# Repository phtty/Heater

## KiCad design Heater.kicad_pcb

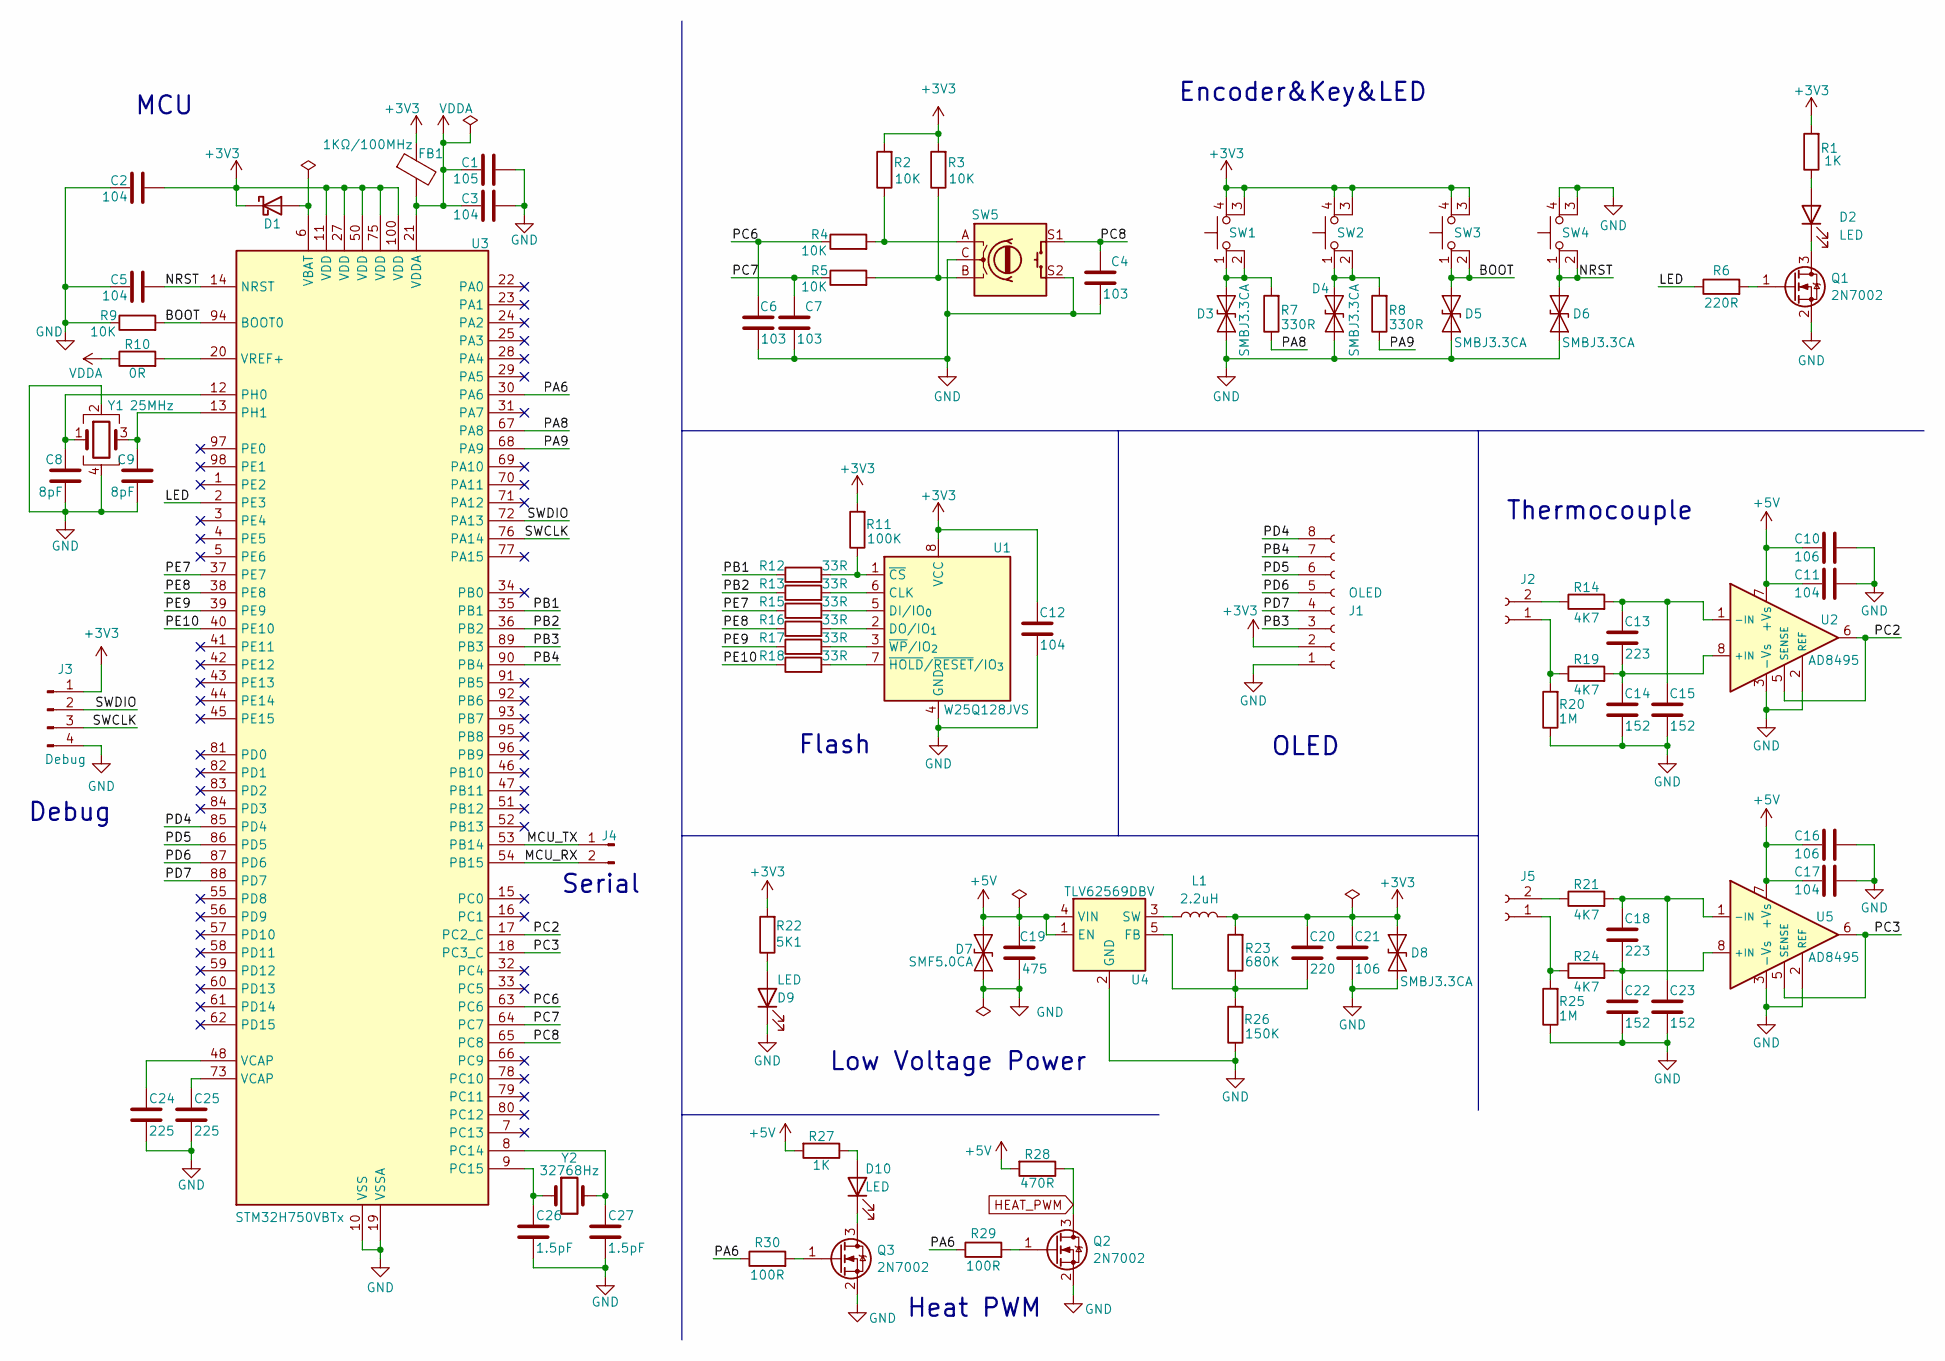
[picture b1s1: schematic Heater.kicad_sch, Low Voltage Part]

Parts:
C1: 105; C_0603_1608Metric_Pad1.08x0.95mm_HandSolder
C2, C3, C5, C11, C12, C17: 104; C_0603_1608Metric_Pad1.08x0.95mm_HandSolder
C4, C6, C7: 103; C_0603_1608Metric_Pad1.08x0.95mm_HandSolder
C8, C9: 8pF; C_0603_1608Metric_Pad1.08x0.95mm_HandSolder
C10, C16, C21: 106; C_0603_1608Metric_Pad1.08x0.95mm_HandSolder
C13, C18: 223; C_0603_1608Metric_Pad1.08x0.95mm_HandSolder
C14, C15, C22, C23: 152; C_0603_1608Metric_Pad1.08x0.95mm_HandSolder
C19: 475; C_0603_1608Metric_Pad1.08x0.95mm_HandSolder
C20: 220; C_0603_1608Metric_Pad1.08x0.95mm_HandSolder
C24, C25: 225; C_0603_1608Metric_Pad1.08x0.95mm_HandSolder
C26, C27: 1.5pF; C_0603_1608Metric_Pad1.08x0.95mm_HandSolder
D1: D_Schottky; D_SOD-123
D2, D9, D10: LED; D_0603_1608Metric_Pad1.05x0.95mm_HandSolder
D3, D4, D5, D6, D8: SMBJ3.3CA; D_SMB_Handsoldering
D7: SMF5.0CA; D_SOD-123F
FB1: 1KΩ/100MHz; C_0603_1608Metric_Pad1.08x0.95mm_HandSolder
J1: OLED; PinHeader_1x08_P2.54mm_Vertical
J2, J5: Conn_01x02_Socket; PinHeader_1x02_P2.54mm_Vertical
J3: Debug; PinHeader_1x04_P2.54mm_Vertical
J4: Conn_01x02_Pin; PinHeader_1x02_P2.54mm_Vertical
L1: 2.2uH; L_0603_1608Metric_Pad1.05x0.95mm_HandSolder
Q1, Q2, Q3: 2N7002; SOT-23_Handsoldering
R1, R27: 1K; R_0603_1608Metric_Pad0.98x0.95mm_HandSolder
R2, R3, R4, R5, R9: 10K; R_0603_1608Metric_Pad0.98x0.95mm_HandSolder
R6: 220R; R_0603_1608Metric_Pad0.98x0.95mm_HandSolder
R7, R8: 330R; R_0603_1608Metric_Pad0.98x0.95mm_HandSolder
R10: 0R; R_0603_1608Metric_Pad0.98x0.95mm_HandSolder
R11: 100K; R_0603_1608Metric_Pad0.98x0.95mm_HandSolder
R12, R13, R15, R16, R17, R18: 33R; R_0603_1608Metric_Pad0.98x0.95mm_HandSolder
R14, R19, R21, R24: 4K7; R_0603_1608Metric_Pad0.98x0.95mm_HandSolder
R20, R25: 1M; R_0603_1608Metric_Pad0.98x0.95mm_HandSolder
R22: 5K1; R_0603_1608Metric_Pad0.98x0.95mm_HandSolder
R23: 680K; R_0603_1608Metric_Pad0.98x0.95mm_HandSolder
R26: 150K; R_0603_1608Metric_Pad0.98x0.95mm_HandSolder
R28: 470R; R_0603_1608Metric_Pad0.98x0.95mm_HandSolder
R29, R30: 100R; R_0603_1608Metric_Pad0.98x0.95mm_HandSolder
SW1, SW2, SW3, SW4: SW_MEC_5E; SW_Buttom_SMD_5.1mmx5.1mm
SW5: RotaryEncoder_Switch; RotaryEncoder_Switch_EC11_SMD
U1: W25Q128JVS; SOIC-8_5.3x5.3mm_P1.27mm
U2, U5: AD8495; MSOP-8_3x3mm_P0.65mm
U3: STM32H750VBTx; LQFP-100_14x14mm_P0.5mm
U4: TLV62569DBV; SOT-23-5
Y1: 25MHz; Crystal_SMD_3225-4Pin_3.2x2.5mm_HandSoldering
Y2: 32768Hz; Crystal_SMD_3215-2Pin_3.2x1.5mm

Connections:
+3V3: C2.2, C12.2, C20.2, C21.2, D1.1 (K), D8.1 (A1), FB1.1, J1.2, J3.1, L1.2, R1.2, R2.2, R3.2, R11.2, R22.2, R23.2, SW1.3 (K), SW1.4 (A), SW2.3 (K), SW2.4 (A), SW3.3 (K), SW3.4 (A), U1.8 (VCC), U3.11 (VDD), U3.27 (VDD), U3.50 (VDD), U3.75 (VDD), U3.100 (VDD)
+5V: C10.2, C11.2, C16.2, C17.2, C19.2, D7.2 (A2), R27.2, R28.2, U2.7 (+Vs), U4.1 (EN), U4.4 (VIN), U5.7 (+Vs); also elsewhere on the board
/BOOT: D5.1 (A1), R9.2, SW3.1, SW3.2, U3.94 (BOOT0)
/LED: R6.1, U3.2 (PE3)
/MCU_RX: J4.2, U3.54 (PB15)
/MCU_TX: J4.1, U3.53 (PB14)
/NRST: C5.2, D6.1 (A1), SW4.1, SW4.2, U3.14 (NRST)
/PA6: R29.1, R30.1, U3.30 (PA6)
/PA8: R7.1, U3.67 (PA8)
/PA9: R8.1, U3.68 (PA9)
/PB1: R12.1, U3.35 (PB1)
/PB2: R13.1, U3.36 (PB2)
/PB3: J1.3, U3.89 (PB3)
/PB4: J1.7, U3.90 (PB4)
/PC2: U2.5 (SENSE), U2.6, U3.17 (PC2_C)
/PC3: U3.18 (PC3_C), U5.5 (SENSE), U5.6
/PC6: C6.2, R4.1, U3.63 (PC6)
/PC7: C7.2, R5.1, U3.64 (PC7)
/PC8: C4.2, SW5.S1, U3.65 (PC8)
/PD4: J1.8, U3.85 (PD4)
/PD5: J1.6, U3.86 (PD5)
/PD6: J1.5, U3.87 (PD6)
/PD7: J1.4, U3.88 (PD7)
/PE7: R15.1, U3.37 (PE7)
/PE8: R16.1, U3.38 (PE8)
/PE9: R17.1, U3.39 (PE9)
/PE10: R18.1, U3.40 (PE10)
/SWCLK: J3.3, U3.76 (PA14)
/SWDIO: J3.2, U3.72 (PA13)
GND: C1.2, C2.1, C3.2, C4.1, C5.1, C6.1, C7.1, C8.2, C9.2, C10.1, C11.1, C12.1, C14.1, C15.1, C16.1, C17.1, C19.1, C21.1, C22.1, C23.1, C24.2, C25.2, C26.2, C27.2, D3.2 (A2), D4.2 (A2), D5.2 (A2), D6.2 (A2), D7.1 (A1), D8.2 (A2), D9.1 (K), J1.1, J3.4, Q1.2 (S), Q2.2 (S), Q3.2 (S), R9.1, R20.1, R25.1, R26.1, SW4.3 (K), SW4.4 (A), SW5.C, SW5.S2, U1.4 (GND), U2.2 (REF), U2.3 (-Vs), U3.10 (VSS), U3.19 (VSSA), U3.26 (VSS), U3.49 (VSS), U3.74 (VSS), U3.99 (VSS), U4.2 (GND), U5.2 (REF), U5.3 (-Vs), Y1.2, Y1.4; also elsewhere on the board
HEAT_PWM: Q2.3 (D), R28.1; also elsewhere on the board
unnamed: C24.1, U3.48 (VCAP)
unnamed: C25.1, U3.73 (VCAP)
unnamed: D1.2 (A), U3.6 (VBAT)
unnamed: D2.2 (A), R1.1
unnamed: D2.1 (K), Q1.3 (D)
unnamed: D3.1 (A1), R7.2, SW1.1, SW1.2
unnamed: D4.1 (A1), R8.2, SW2.1, SW2.2
unnamed: D9.2 (A), R22.1
unnamed: D10.2 (A), R27.1
unnamed: D10.1 (K), Q3.3 (D)
unnamed: J2.1, R19.1, R20.2
unnamed: J2.2, R14.1
unnamed: J5.1, R24.1, R25.2
unnamed: J5.2, R21.1
unnamed: Q1.1 (G), R6.2
unnamed: Q2.1 (G), R29.2
unnamed: Q3.1 (G), R30.2
unnamed: R2.1, R4.2, SW5.A
unnamed: R3.1, R5.2, SW5.B
unnamed: R13.2, U1.6 (CLK)
unnamed: R15.2, U1.5 (DI/IO_{0})
unnamed: R16.2, U1.2 (DO/IO_{1})
unnamed: R11.1, R12.2, U1.1 (~CS)
unnamed: R18.2, U1.7 (~HOLD/~RESET/IO_{3})
unnamed: R17.2, U1.3 (~WP/IO_{2})
unnamed: C13.1, C14.2, R19.2, U2.8 (+IN)
unnamed: C13.2, C15.2, R14.2, U2.1 (-IN)
unnamed: C27.1, U3.8 (PC14), Y2.2
unnamed: C26.1, U3.9 (PC15), Y2.1
unnamed: C8.1, U3.12 (PH0), Y1.1
unnamed: C9.1, U3.13 (PH1), Y1.3
unnamed: R10.2, U3.20 (VREF+)
unnamed: C20.1, R23.1, R26.2, U4.5 (FB)
unnamed: L1.1, U4.3 (SW)
unnamed: C18.1, C22.2, R24.2, U5.8 (+IN)
unnamed: C18.2, C23.2, R21.2, U5.1 (-IN)
VDDA: C1.1, C3.1, FB1.2, R10.1, U3.21 (VDDA)

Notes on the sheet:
OLED
Low Voltage Power
Heat PWM
Thermocouple
Encoder&Key&LED
MCU
Flash
Debug
Serial

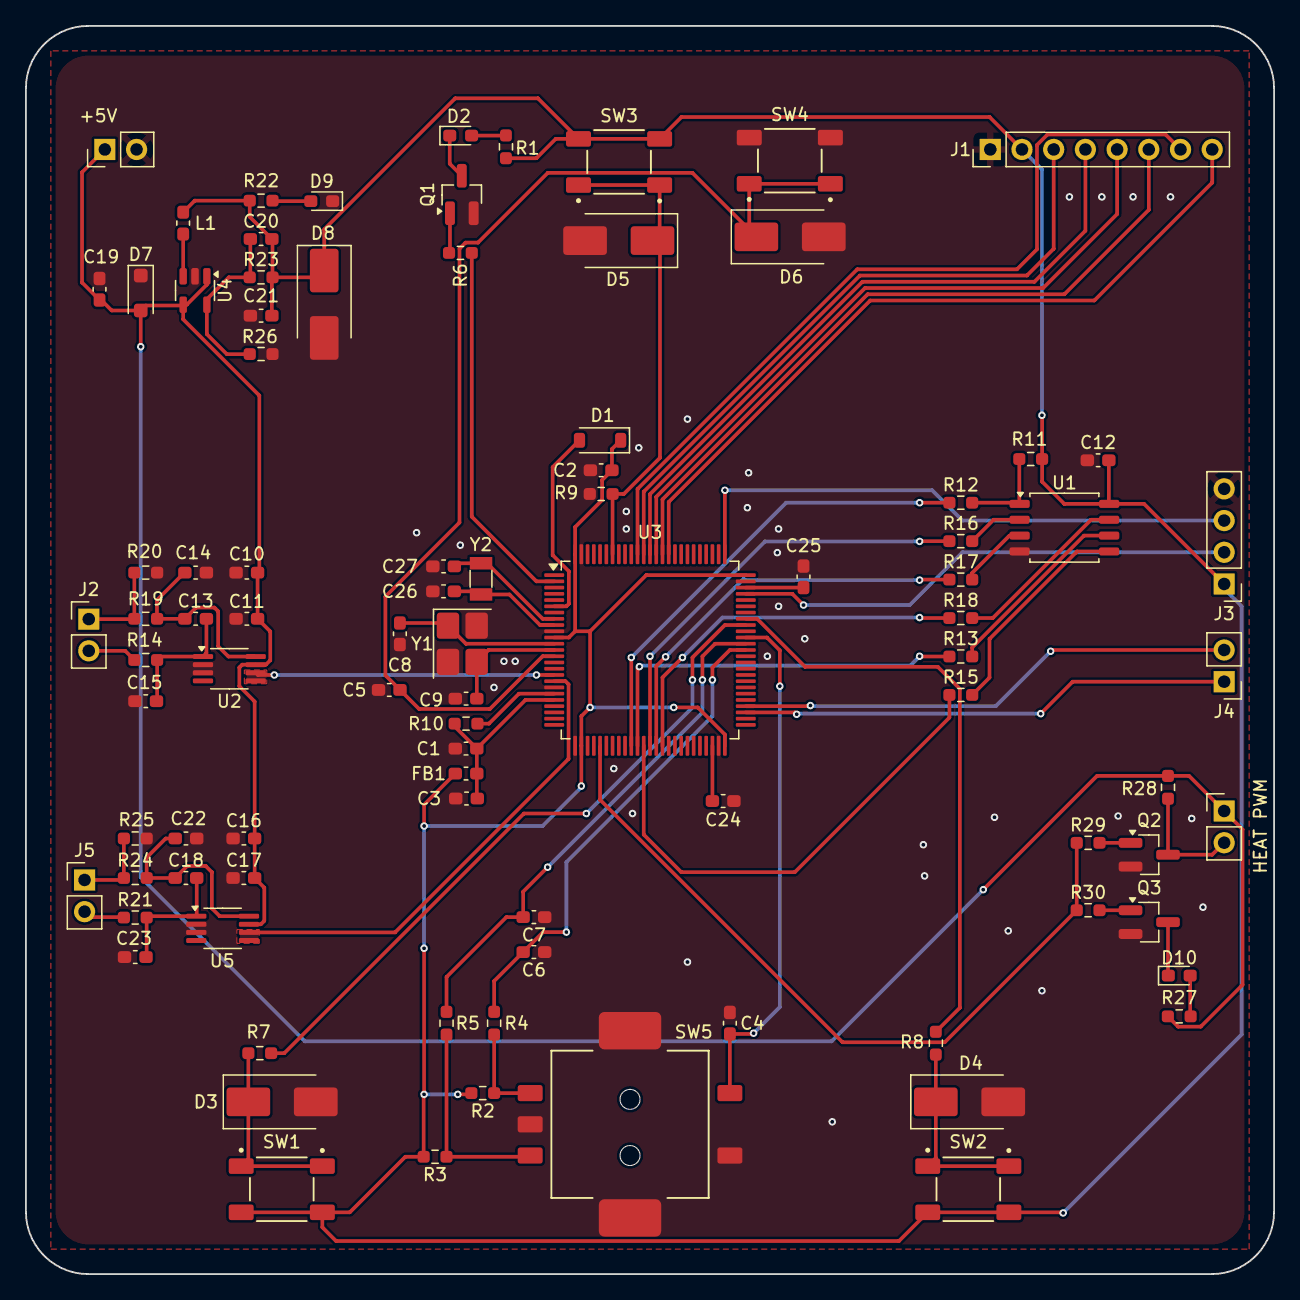
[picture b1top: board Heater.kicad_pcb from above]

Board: 2 copper layers, 100.0 x 100.0 mm, 91 parts (0 on the bottom side), 68 nets.

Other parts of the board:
+5V: PinHeader_1x02_P2.54mm_Vertical
HEAT PWM: PinHeader_1x02_P2.54mm_Vertical

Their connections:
+5V: +5V.1, HEAT PWM.1; also elsewhere on the board
GND: +5V.2; also elsewhere on the board
HEAT_PWM: HEAT PWM.2; also elsewhere on the board

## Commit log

2025-05-27 添加prl文件
2025-05-27 feat: 完成弱电部分的原理图绘制
2025-05-28 fix: 调整了全部元件的位号，并重新设计了加热端的驱动部分
2025-05-28 feat: 完成元件选型和封装设置
2025-05-28 feat: 完成了部分元件的layout
2025-05-29 feat: 完成了PCB的layout，元件库存在部分修改
2025-05-29 fix: 进行一些细节调整
2025-05-30 feat: 添加了BOM表
